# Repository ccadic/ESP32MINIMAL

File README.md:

# ESP32MINIMAL
ESP32 PCB, minimal version

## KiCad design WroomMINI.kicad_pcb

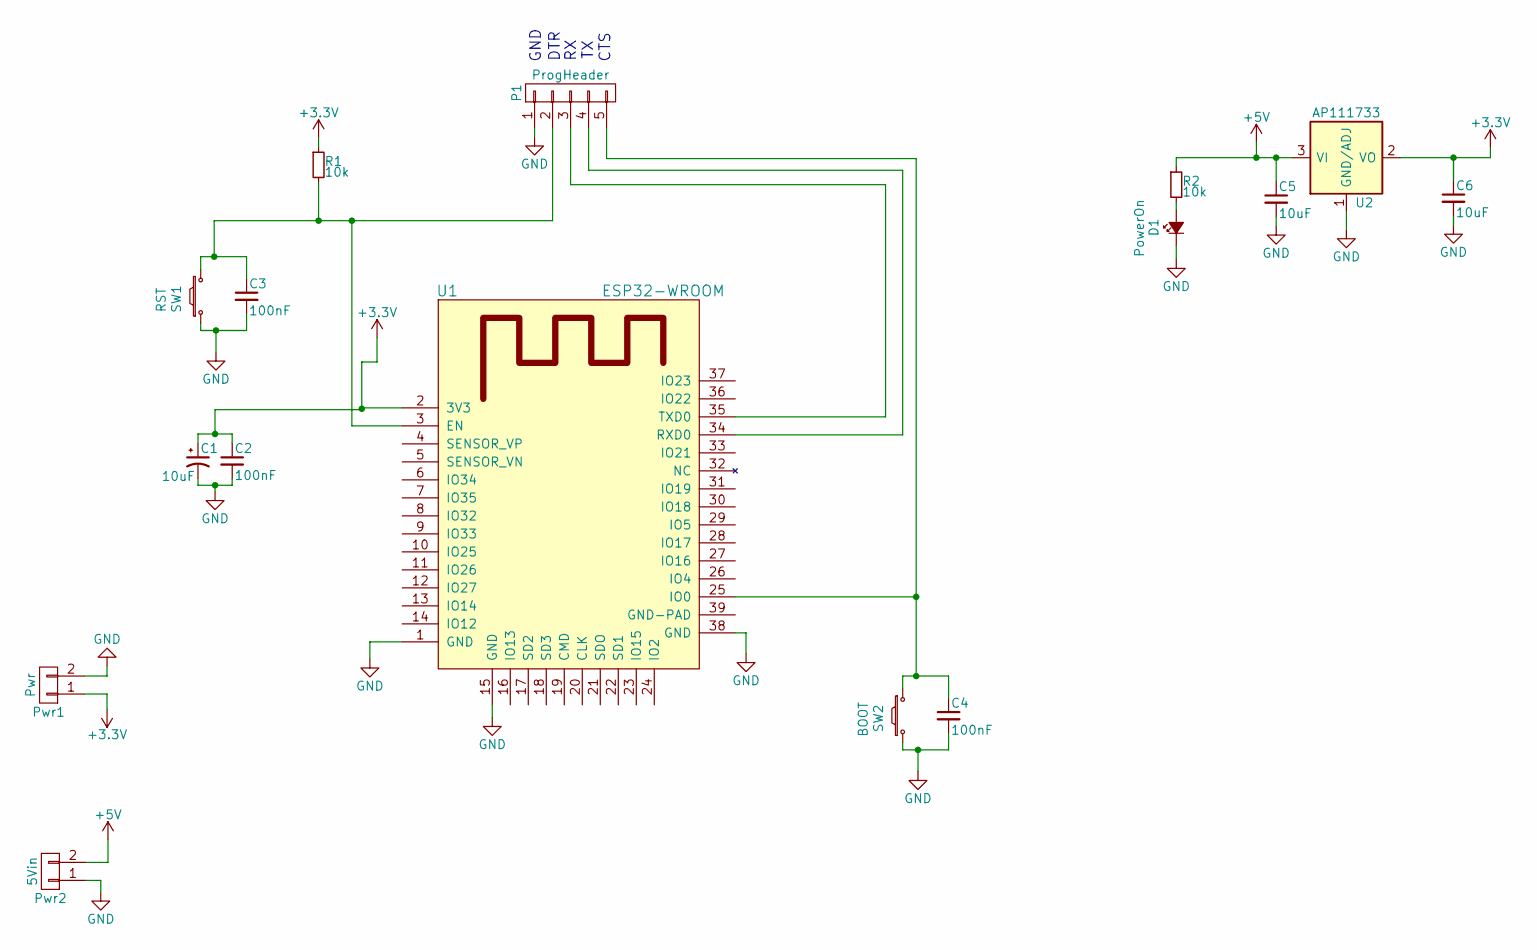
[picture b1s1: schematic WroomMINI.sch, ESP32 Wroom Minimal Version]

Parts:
C1, C5, C6: 10uF; C_1206_HandSoldering
C2, C3, C4: 100nF; C_1206_HandSoldering
D1: PowerOn; LED_1206_HandSoldering
P1: ProgHeader; Socket_Strip_Straight_1x05_Pitch2.54mm
Pwr1: Pwr; Socket_Strip_Straight_1x02_Pitch2.54mm
Pwr2: 5Vin; Socket_Strip_Straight_1x02_Pitch2.54mm
R1, R2: 10k; R_1206_HandSoldering
SW1: RST; SW_SPST_B3U-1000P
SW2: BOOT; SW_SPST_B3U-1000P
U1: ESP32-WROOM
U2: AP111733; SOT-223

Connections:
+3V3: C1.1, C2.1, C6.1, Pwr1.1, R1.1, U1.2 (3V3), U2.2 (VO), U2.4 (VO)
+5V: C5.1, Pwr2.2, R2.1, U2.3 (VI)
GND: C1.2, C2.2, C3.2, C4.2, C5.2, C6.2, D1.1 (K), P1.1, Pwr1.2, Pwr2.1, SW1.1, SW2.1, U1.1 (GND), U1.15 (GND), U1.38 (GND), U2.1 (GND/ADJ)
unnamed: C3.1, P1.2, R1.2, SW1.2, U1.3 (EN)
unnamed: C4.1, P1.5, SW2.2, U1.25 (IO0)
unnamed: D1.2 (A), R2.2
unnamed: P1.3, U1.35 (TXD0)
unnamed: P1.4, U1.34 (RXD0)

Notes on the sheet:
GND
DTR
CTS

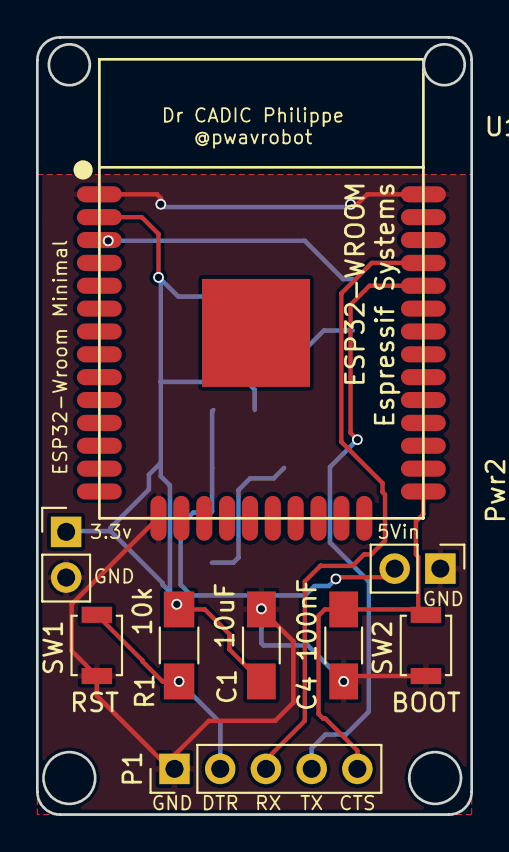
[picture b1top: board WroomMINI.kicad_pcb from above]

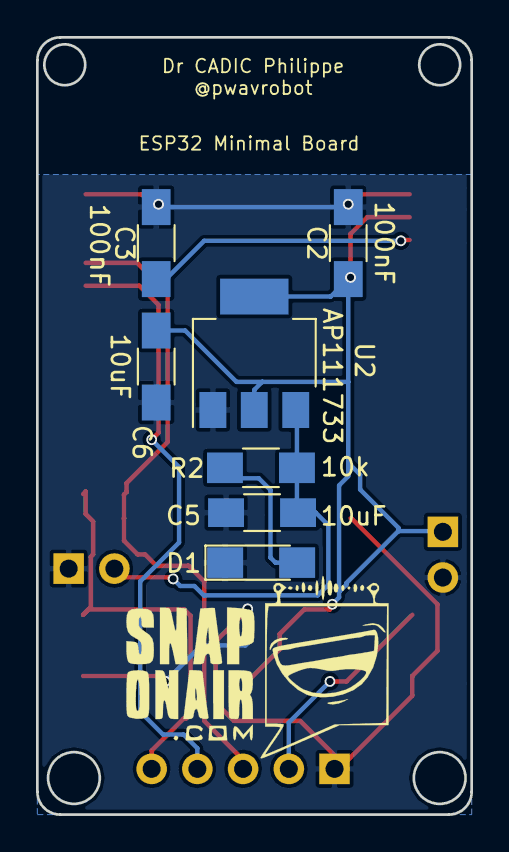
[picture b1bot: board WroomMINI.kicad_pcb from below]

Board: 2 copper layers, 24.1 x 43.2 mm, 16 parts (7 on the bottom side), 8 nets.
